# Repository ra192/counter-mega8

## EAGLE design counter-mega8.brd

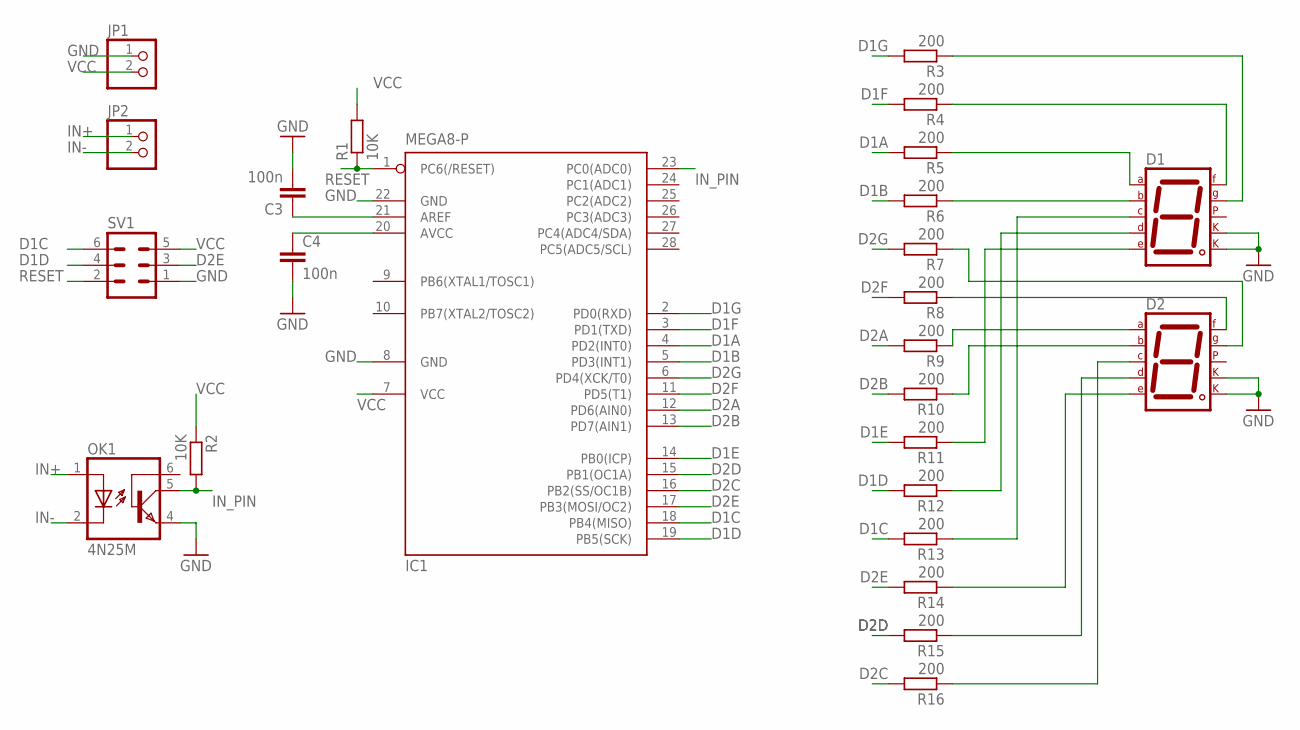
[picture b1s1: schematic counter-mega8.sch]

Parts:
C3, C4: 100n; C1206
D1, D2: 7SEG-CK; 7SEG-13
IC1: MEGA8-P; DIL28-3
JP1, JP2: PINHD-1X2/90; 1X02/90
OK1: 4N25M; DIL06
R1, R2: 10K; R1206
R3, R4, R5, R6, R7, R8, R9, R10, R11, R12, R13, R14, R15, R16: 200; R1206
SV1: MA03-2

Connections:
AVCC: C4.1, IC1.20 (AVCC)
D1A: IC1.4 (PD2(INT0)), R5.2
D1B: IC1.5 (PD3(INT1)), R6.2
D1C: IC1.18 (PB4(MISO)), R13.2, SV1.6
D1D: IC1.19 (PB5(SCK)), R12.2, SV1.4
D1E: IC1.14 (PB0(ICP)), R11.2
D1F: IC1.3 (PD1(TXD)), R4.2
D1G: IC1.2 (PD0(RXD)), R3.2
D2A: IC1.12 (PD6(AIN0)), R9.2
D2B: IC1.13 (PD7(AIN1)), R10.2
D2C: IC1.16 (PB2(SS/OC1B)), R16.2
D2D: IC1.15 (PB1(OC1A)), R15.2
D2E: IC1.17 (PB3(MOSI/OC2)), R14.2, SV1.3
D2F: IC1.11 (PD5(T1)), R8.2
D2G: IC1.6 (PD4(XCK/T0)), R7.2
GND: C3.2, C4.2, D1.3 (CK1), D1.8 (CK2), D2.3 (CK1), D2.8 (CK2), IC1.8 (GND), IC1.22 (GND), JP1.1, OK1.4 (EMI), SV1.1
IN+: JP2.1, OK1.1 (A)
IN-: JP2.2, OK1.2 (C)
IN_PIN: IC1.23 (PC0(ADC0)), OK1.5 (COL), R2.2
unnamed: C3.1, IC1.21 (AREF)
unnamed: D1.1 (E), R11.1
unnamed: D1.2 (D), R12.1
unnamed: D1.4 (C), R13.1
unnamed: D2.1 (E), R14.1
unnamed: D2.2 (D), R15.1
unnamed: D2.4 (C), R16.1
unnamed: D1.9 (F), R4.1
unnamed: D1.7 (A), R5.1
unnamed: D1.6 (B), R6.1
unnamed: D2.10 (G), R7.1
unnamed: D2.9 (F), R8.1
unnamed: D2.7 (A), R9.1
unnamed: D2.6 (B), R10.1
unnamed: D1.10 (G), R3.1
RESET: IC1.1 (PC6(/RESET)), R1.1, SV1.2
VCC: IC1.7 (VCC), JP1.2, R1.2, R2.1, SV1.5

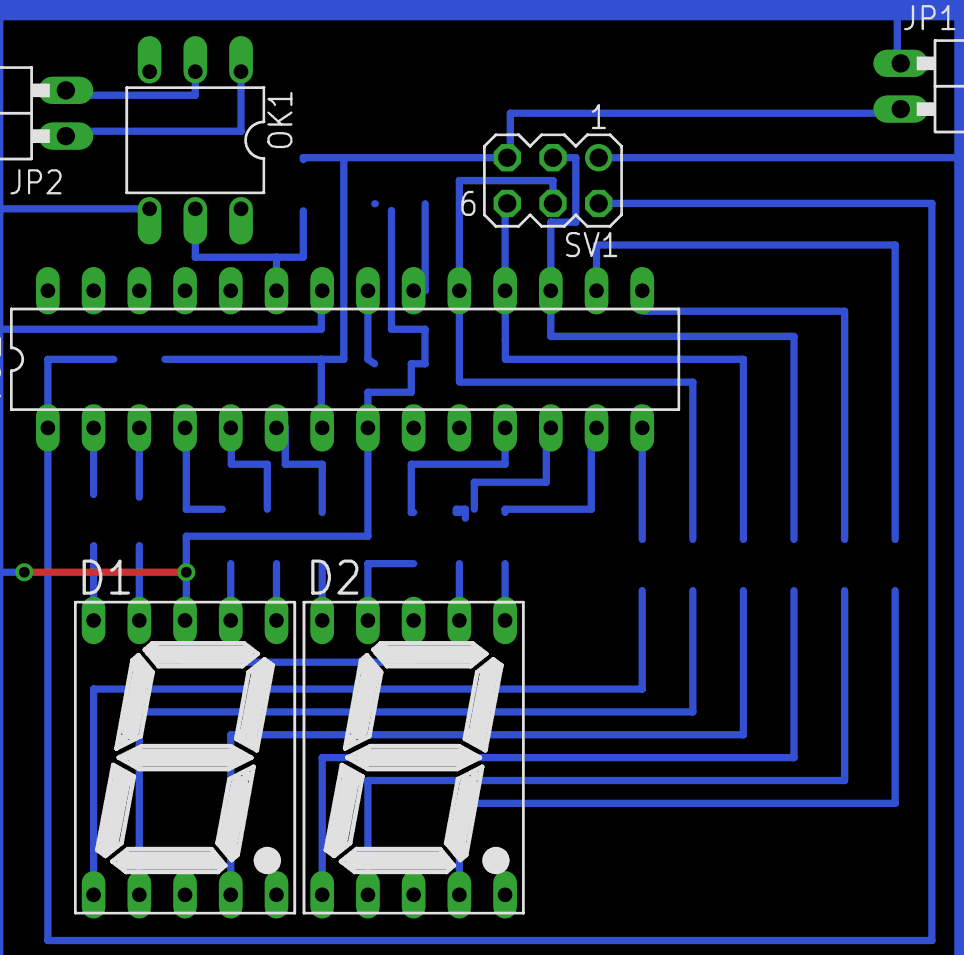
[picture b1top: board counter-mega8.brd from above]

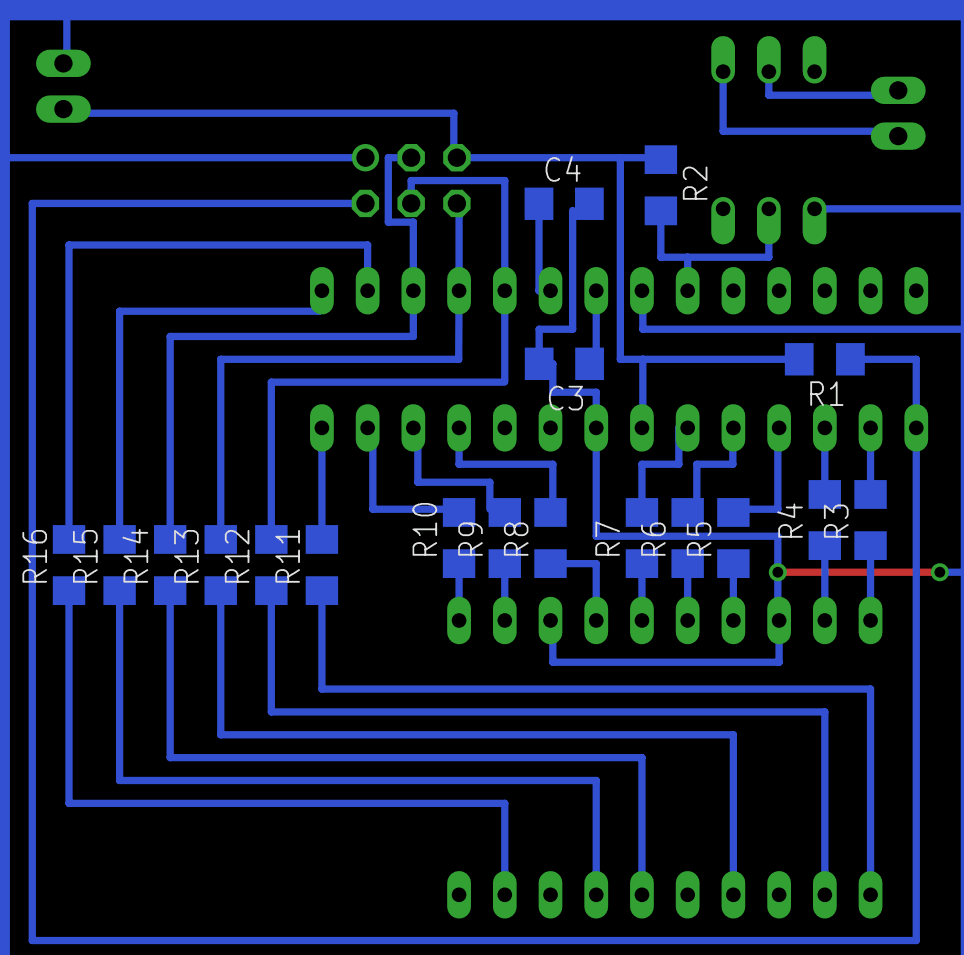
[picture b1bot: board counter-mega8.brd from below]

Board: 2 copper layers, 25 parts (18 on the bottom side), 36 nets.

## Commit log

2015-10-25 add firmware source
2015-10-25 add firmware
